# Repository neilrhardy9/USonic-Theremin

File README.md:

# USonic-Theremin
A portable, rechargeable theremin using ultrasonic transducers for distance sensing. Connect the device to any consumer-grade speaker or directly to your computer to record your sound!

Take a look at the <a href="Schematic_Capture.pdf">schematic<a/>
  
Feedback and derivatives are welcome! **NOTE** that the firmware files are licensed under a permissive MIT OSL, but the **hardware is licensed under a strongly reciprocal CERN-OHL-S license** which means all derivatives must undertake the same license.

Thanks,
Neil

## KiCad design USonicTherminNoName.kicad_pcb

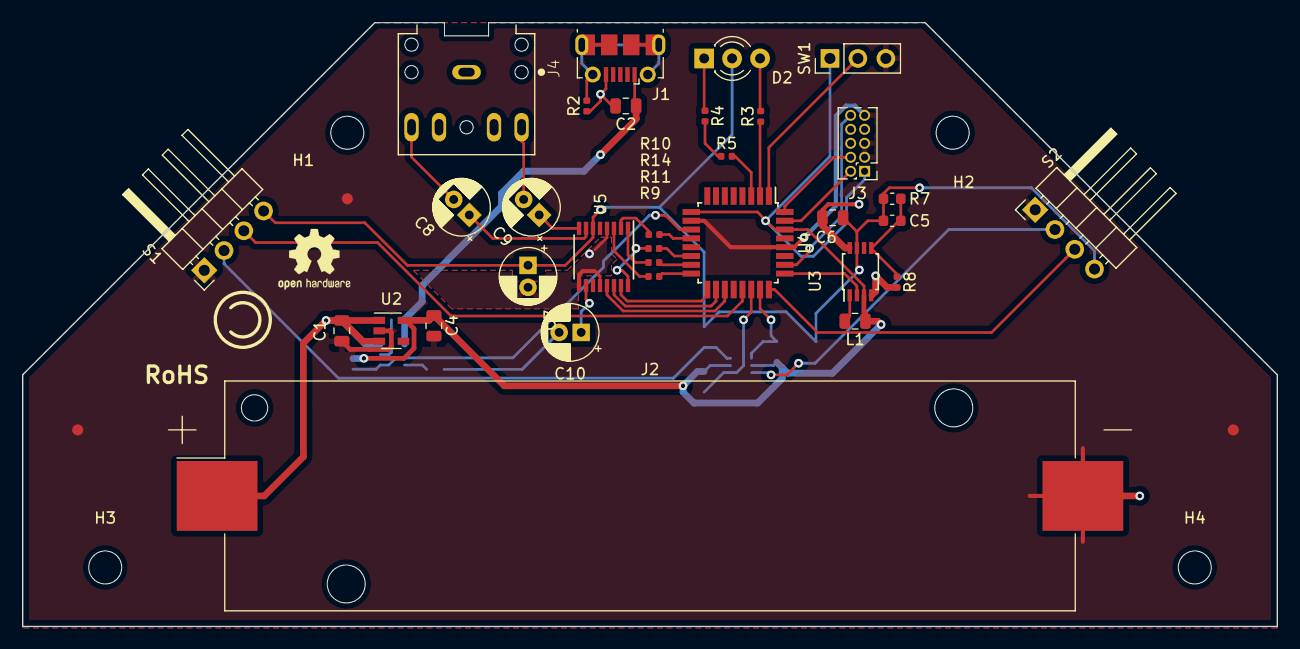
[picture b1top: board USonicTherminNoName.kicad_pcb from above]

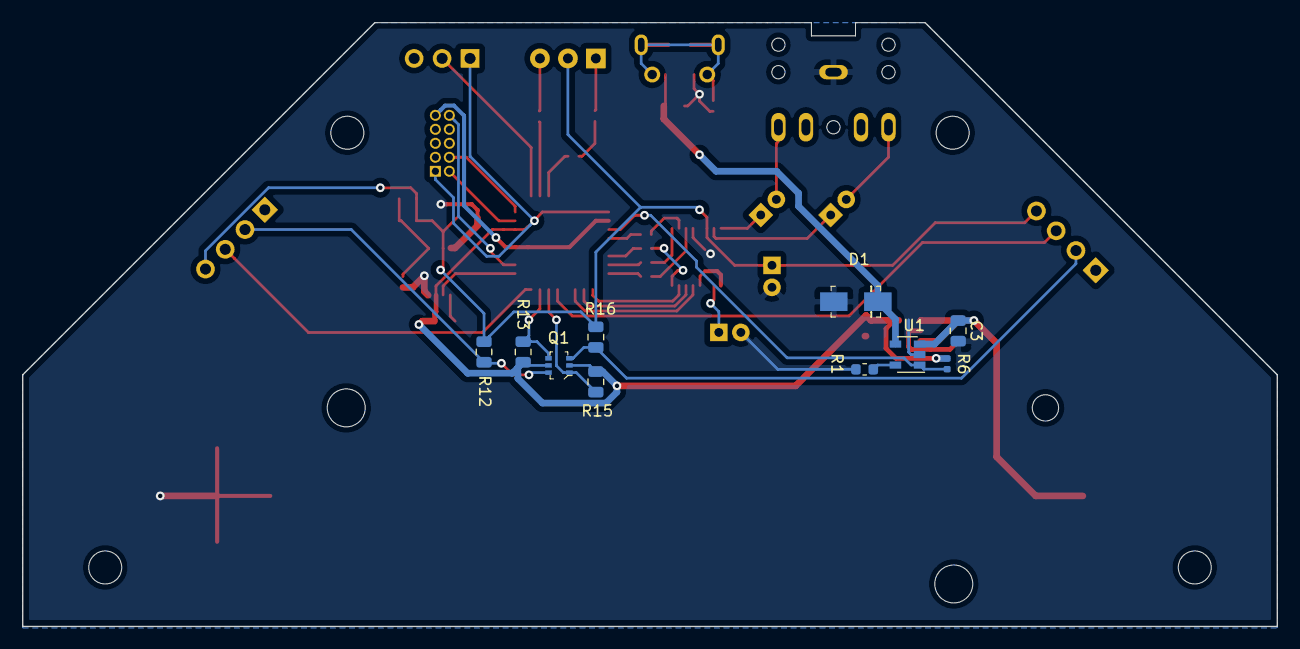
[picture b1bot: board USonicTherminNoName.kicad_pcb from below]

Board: 2 copper layers, 114.0 x 54.9 mm, 50 parts (10 on the bottom side), 43 nets.

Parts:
 : Fiducial_1mm_Mask2mm
 #2,  #3: Fiducial_1mm_Mask2mm
 #4: CC-ShareAlike; Symbol_CC-ShareAlike_CopperTop_Small
C1, C2, C3, C4: 10u; C_0805_2012Metric
C5: 1n; C_0603_1608Metric
C6: 22u; C_0805_2012Metric
C7, C8, C9, C10: 10u; CP_Radial_D5.0mm_P2.00mm
D1: D_Schottky; DO-214AC
D2: LED_Dual_CAC; LED_D3.0mm-3
H1: 3mm; MountingHole_3mm
H2, H3, H4: MountingHole_3mm
J1: USB_B_Micro; USB_Micro-B_Molex-105017-0001
J2: Li Battery; BatteryHolder_Keystone_1042_1x18650
J3: JTAG; PinHeader_2x05_P1.27mm_Vertical
J4: SJ1-3525N; CUI_SJ1-3525N
L1: 2.2u; L_0805_2012Metric
Q1: BSS138DW; SOT-363
R1: 2k; R_0603_1608Metric
R2, R6, R8: 100k; R_0402_1005Metric
R3, R4, R5, R9, R10, R11, R14: 100; R_0402_1005Metric
R7: 750k; R_0603_1608Metric
R12, R13, R15, R16: 10k; R_0805_2012Metric
S1, S2: HC-SR04; PinHeader_1x04_P2.54mm_Horizontal
SW1: SW_SPDT; PinHeader_1x03_P2.54mm_Vertical
U1: MCP73831; SOT-23-5
U2: XC6220B331MR; SOT-23-5
U3: PAM2401; TSSOP-8_3x3mm_P0.65mm
U4: ATSAMD21E17A; TQFP-32_7x7mm_P0.8mm
U5: PCM1754DBQR; SSOP-16_3.9x4.9mm_P0.635mm

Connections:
/3.3V: C4.1, J3.1, L1.1, Q1.2, Q1.5, R6.2, R13.2, R15.2, SW1.1, U2.5, U3.3, U4.9, U4.30
/5V: C5.1, C6.1, C7.1, D2.2, R7.1, R12.2, R16.2, S1.4, S2.4, U3.7, U5.6
/BCK: R11.2, U4.15
/BLUE: R3.1, U4.2
/BUTTON: SW1.2, U4.1
/DATA: R10.2, U4.12
/DEMP: U4.19, U5.13
/ECHO1: Q1.3, R16.1, S1.2
/ECHO1S: Q1.4, R13.1, U4.23
/ECHO2: Q1.6, R12.1, S2.2
/ECHO2S: Q1.1, R15.1, U4.22
/ENABLE: U3.2, U4.25
/FMT: U4.17, U5.15
/LRCK: R9.2, U4.16
/MUTE: U4.18, U5.14
/RED: R5.2, U4.3
/SCK: R14.1, U4.14
/STAT: R6.1, U1.1, U4.11
/SWD_CLK: J3.4, U4.32
/SWD_DATA: J3.2, U4.31
/TRIG1: S1.3, U4.21
/TRIG2: S2.3, U4.24
/VBAT: C1.1, C3.1, J2.1, U1.3, U2.1, U2.3
/VBUS: C2.1, D1.1, J1.1, U1.4
/VCOM: C10.1, U5.10
/VOUTL: C8.2, J4.2
/VOUTR: C9.2, J4.3
/XRES: J3.10, U4.26
GNDA: C2.2, C3.2, C6.2, C7.2, C10.2, D1.2, J1.5, J2.2, J4.1, R1.2, R2.1, R8.2, U1.2, U3.4, U3.8, U5.4, U5.9, U5.12
GNDD: C1.2, C4.2, J3.3, J3.5, J3.9, S1.1, S2.1, SW1.3, U2.2, U4.10, U4.28
unnamed: C5.2, R7.2, R8.1, U3.5
unnamed: C8.1, U5.7
unnamed: C9.1, U5.8
unnamed: D2.1, R4.1
unnamed: D2.3, R3.2
unnamed: J1.6, R2.2
unnamed: L1.2, U3.1
unnamed: R1.1, U1.5
unnamed: R4.2, R5.1
unnamed: R9.1, U5.3
unnamed: R10.1, U5.2
unnamed: R11.1, U5.1
unnamed: R14.2, U5.16

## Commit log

2020-12-02 Uploaded KiCAD project, board, and gerber files
    I'm late to documenting the project, but better than never
2020-12-02 Made a README
2020-12-02 organizing into folder
2020-12-02 put files in KiCAD directory
2020-12-03 added progress pics
2020-12-03 included pics in readme
